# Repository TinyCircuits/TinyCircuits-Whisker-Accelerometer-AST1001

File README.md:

# TinyCircuits Accelerometer Wireling Board
# AST1001 Rev1

The design files are located under design_files/ for the TinyCircuits ASD2205 Rev 2 PCB.  This is a Wireling board that has a BMA250 Accelerometer. 

Format is in Cadsoft Eagle format - Eagle version 6.2 was used for the original design.

For more infomation on this, check out the product page at TinyCircuits.com:  https://tinycircuits.com/products/microsd-tinyshield

# License:

Design by TinyCircuits.
All design files are released under the Creative Commons Attribution Share-Alike 3.0 License, see the following link for details: http://creativecommons.org/licenses/by-sa/3.0

All text above must be included in any redistribution or derived design

This project uses designs and concepts developed as part of the Arduino project and the LilyPad project.  The TinyCircuits design files themselves (schematics, PCB and libraries) are not directly derived from these works' design files and have been created new, however the concepts and basic architecture behind the TinyDuino and TinyLily products are derived and we thank the hard work of the organizations below for their contributions to open-source hardware:
  
Original Arduino Uno Design by Team Arduino

LilyPad Arduino Design by Leah Buechley and Sparkfun Electronics

Please support the open-source hardware community

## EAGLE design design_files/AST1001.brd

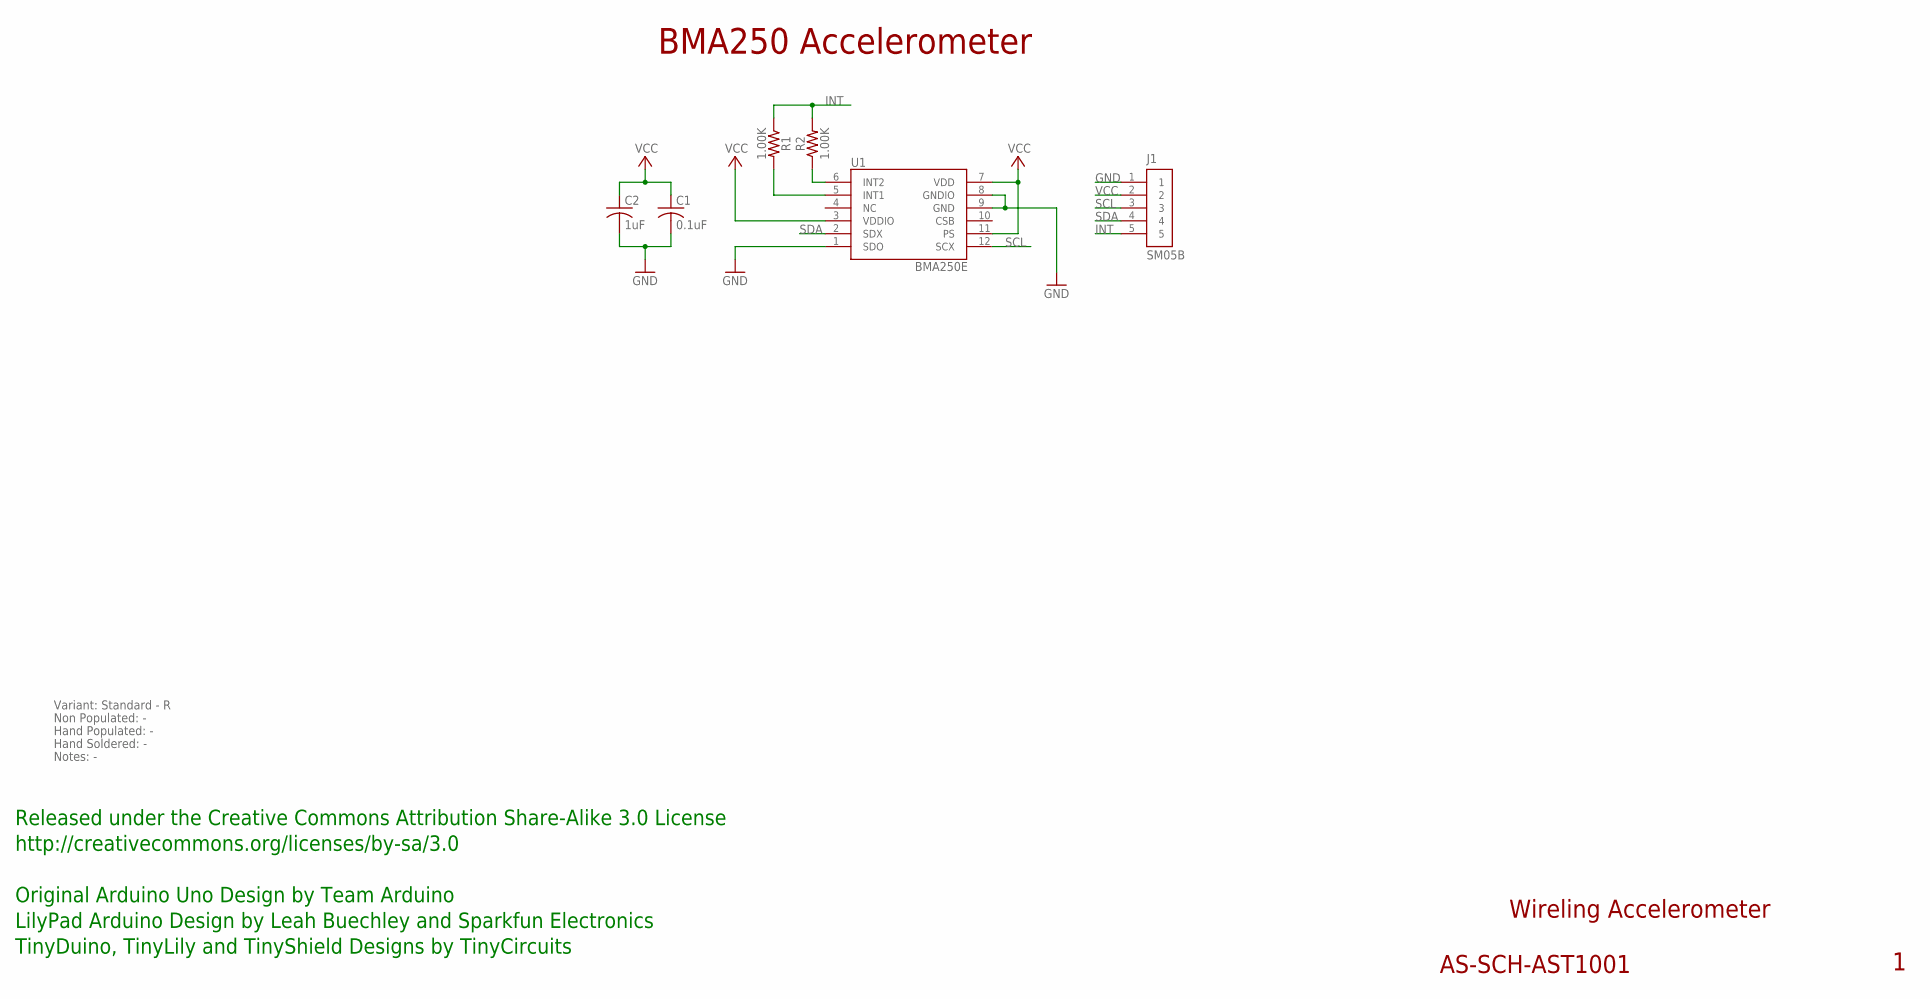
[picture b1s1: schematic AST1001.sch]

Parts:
C1: 0.1uF; C0402
C2: 1uF; C0603; PARTNO AS-ITM-00410
J1: SM05B; JST_SH_5X1_EDGE
R1, R2: 1.00K; 0402; PARTNO AS-ITM-00003
U1: BMA250E; 3-AXIS_ACCELEROMETER

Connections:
GND: C1.2, C2.2, J1.1, U1.1 (SDO), U1.8 (GNDIO), U1.9 (GND)
INT: J1.5, R1.1, R2.2
unnamed: R1.2, U1.5 (INT1)
unnamed: R2.1, U1.6 (INT2)
SCL: J1.3, U1.12 (SCX)
SDA: J1.4, U1.2 (SDX)
VCC: C1.1, C2.1, J1.2, U1.3 (VDDIO), U1.7 (VDD), U1.11 (PS)

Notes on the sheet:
Wireling Accelerometer
AS-SCH-AST1001
BMA250 Accelerometer
Released under the Creative Commons Attribution Share-Alike 3.0 License
http://creativecommons.org/licenses/by-sa/3.0
Original Arduino Uno Design by Team Arduino
TinyDuino, TinyLily and TinyShield Designs by TinyCircuits
LilyPad Arduino Design by Leah Buechley and Sparkfun Electronics
Non Populated: -
Hand Populated: -
Hand Soldered: -
Variant: Standard - R
Notes: -

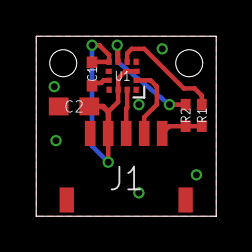
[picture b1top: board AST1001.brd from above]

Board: 2 copper layers, 10.0 x 10.0 mm, 7 parts (0 on the bottom side), 7 nets.

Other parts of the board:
U$1: DOCFIELD-TINYCIRCUITS-PCB

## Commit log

2019-07-30 updated to use Port 0
2019-08-02 added datasheet
2019-09-24 fix program comment
2019-09-24 image
2019-12-30 updated documentation
2020-01-31 photo
2020-02-04 mass image update
2020-04-15 Double Tape example
2020-08-14 Add CAD data
2020-12-18 rename datasheet as flier
2020-12-18 added complete datasheet
